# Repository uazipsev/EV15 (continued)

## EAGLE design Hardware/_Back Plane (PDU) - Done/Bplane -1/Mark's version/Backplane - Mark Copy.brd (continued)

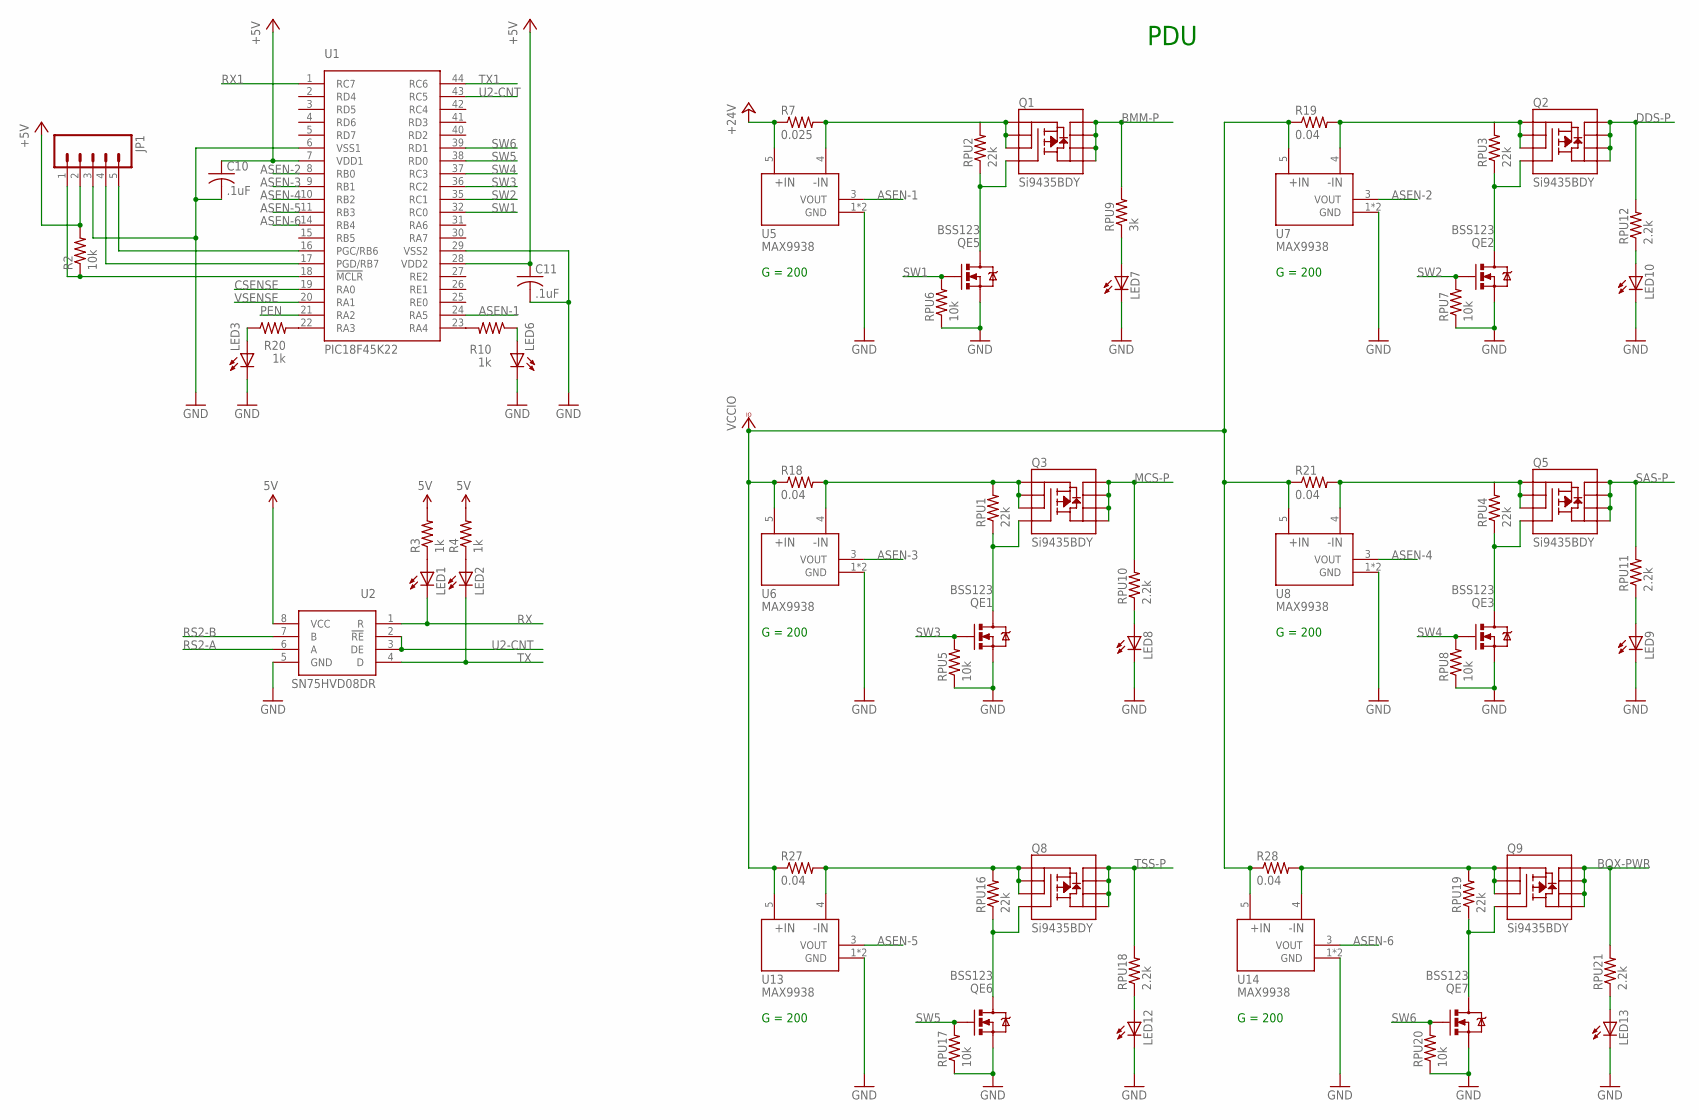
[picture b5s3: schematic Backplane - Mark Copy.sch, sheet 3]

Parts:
C10, C11: .1uF; C0805
JP1: M05LOCK_LONGPADS; 1X05_LOCK_LONGPADS
LED1, LED2, LED3, LED6, LED7, LED8, LED9, LED10, LED12, LED13: LEDCHIP-LED0805; CHIP-LED0805
Q1, Q2, Q3, Q5, Q8, Q9: Si9435BDY; SO08
QE1, QE2, QE3, QE5, QE6, QE7: BSS123; SOT-23
R2: 10k; 0805
R3, R4, R10, R20: 1k; R0805
R7: 0.025; R6332
R18, R19, R21, R27, R28: 0.04; R6332
RPU1, RPU2, RPU3, RPU4, RPU16, RPU19: 22k; 0805
RPU5, RPU6, RPU7, RPU8, RPU17, RPU20: 10k; 0805
RPU9: 3k; 0805
RPU10, RPU11, RPU12, RPU18, RPU21: 2.2k; 0805
U1: PIC18F45K22; TQFP-44
U2: SN75HVD08DR; SO-8
U5, U6, U7, U8, U13, U14: MAX9938; SOT23-5

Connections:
5V: R3.2, R4.2, U2.8 (VCC); also elsewhere on the board
+5V: C10.1, C11.1, JP1.2, R2.2, U1.7 (VDD1), U1.28 (VDD2); also elsewhere on the board
+24V: R7.1, U5.5 (+IN); also elsewhere on the board
ASEN-1: U1.24 (RA5), U5.3 (VOUT)
ASEN-2: U1.8 (RB0), U7.3 (VOUT)
ASEN-3: U1.9 (RB1), U6.3 (VOUT)
ASEN-4: U1.10 (RB2), U8.3 (VOUT)
ASEN-5: U1.11 (RB3), U13.3 (VOUT)
ASEN-6: U1.14 (RB4), U14.3 (VOUT)
BMM-P: Q1.5 (D), Q1.6 (D), Q1.7 (D), Q1.8 (D), RPU9.2; also elsewhere on the board
BOX-PWR: Q9.5 (D), Q9.6 (D), Q9.7 (D), Q9.8 (D), RPU21.2; also elsewhere on the board
CSENSE: U1.19 (RA0); also elsewhere on the board
DDS-P: Q2.5 (D), Q2.6 (D), Q2.7 (D), Q2.8 (D), RPU12.2; also elsewhere on the board
GND: C10.2, C11.2, JP1.3, LED3.C, LED6.C, LED7.C, LED8.C, LED9.C, LED10.C, LED12.C, LED13.C, QE1.2 (S), QE2.2 (S), QE3.2 (S), QE5.2 (S), QE6.2 (S), QE7.2 (S), RPU5.1, RPU6.1, RPU7.1, RPU8.1, RPU17.1, RPU20.1, U1.6 (VSS1), U1.29 (VSS2), U2.5 (GND), U5.1 (GND), U5.2 (GND), U6.1 (GND), U6.2 (GND), U7.1 (GND), U7.2 (GND), U8.1 (GND), U8.2 (GND), U13.1 (GND), U13.2 (GND), U14.1 (GND), U14.2 (GND); also elsewhere on the board
MCS-P: Q3.5 (D), Q3.6 (D), Q3.7 (D), Q3.8 (D), RPU10.2; also elsewhere on the board
unnamed: Q1.4 (G), QE5.3 (D), RPU2.1
unnamed: Q8.1 (S), Q8.2 (S), Q8.3 (S), R27.2, RPU16.2, U13.4 (-IN)
unnamed: Q3.1 (S), Q3.2 (S), Q3.3 (S), R18.2, RPU1.2, U6.4 (-IN)
unnamed: Q3.4 (G), QE1.3 (D), RPU1.1
unnamed: Q2.1 (S), Q2.2 (S), Q2.3 (S), R19.2, RPU3.2, U7.4 (-IN)
unnamed: LED3.A, R20.1
unnamed: LED7.A, RPU9.1
unnamed: Q2.4 (G), QE2.3 (D), RPU3.1
unnamed: R20.2, U1.22 (RA3)
unnamed: LED8.A, RPU10.1
unnamed: LED9.A, RPU11.1
unnamed: LED1.A, R3.1
unnamed: LED2.A, R4.1
unnamed: Q5.1 (S), Q5.2 (S), Q5.3 (S), R21.2, RPU4.2, U8.4 (-IN)
unnamed: Q5.4 (G), QE3.3 (D), RPU4.1
unnamed: LED10.A, RPU12.1
unnamed: Q8.4 (G), QE6.3 (D), RPU16.1
unnamed: Q1.1 (S), Q1.2 (S), Q1.3 (S), R7.2, RPU2.2, U5.4 (-IN)
unnamed: LED12.A, RPU18.1
unnamed: Q9.1 (S), Q9.2 (S), Q9.3 (S), R28.2, RPU19.2, U14.4 (-IN)
unnamed: Q9.4 (G), QE7.3 (D), RPU19.1
unnamed: JP1.4, U1.17 (PGD/RB7)
unnamed: JP1.5, U1.16 (PGC/RB6)
unnamed: LED13.A, RPU21.1
unnamed: JP1.1, R2.1, U1.18 (!MCLR)
unnamed: LED6.A, R10.1
unnamed: R10.2, U1.23 (RA4)
PEN: U1.21 (RA2)
RS2-A: U2.6 (A); also elsewhere on the board
RS2-B: U2.7 (B); also elsewhere on the board
RX: LED1.C, U2.1 (R)
RX1: U1.1 (RC7)
SAS-P: Q5.5 (D), Q5.6 (D), Q5.7 (D), Q5.8 (D), RPU11.2; also elsewhere on the board
SW1: QE5.1 (G), RPU6.2, U1.32 (RC0)
SW2: QE2.1 (G), RPU7.2, U1.35 (RC1)
SW3: QE1.1 (G), RPU5.2, U1.36 (RC2)
SW4: QE3.1 (G), RPU8.2, U1.37 (RC3)
SW5: QE6.1 (G), RPU17.2, U1.38 (RD0)
SW6: QE7.1 (G), RPU20.2, U1.39 (RD1)
TSS-P: Q8.5 (D), Q8.6 (D), Q8.7 (D), Q8.8 (D), RPU18.2; also elsewhere on the board
TX: LED2.C, U2.4 (D)
TX1: U1.44 (RC6)
U2-CNT: U1.43 (RC5), U2.2 (!RE), U2.3 (DE)
VCCIO: R18.1, R19.1, R21.1, R27.1, R28.1, U6.5 (+IN), U7.5 (+IN), U8.5 (+IN), U13.5 (+IN), U14.5 (+IN); also elsewhere on the board
VSENSE: U1.20 (RA1); also elsewhere on the board

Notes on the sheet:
PDU
G = 200

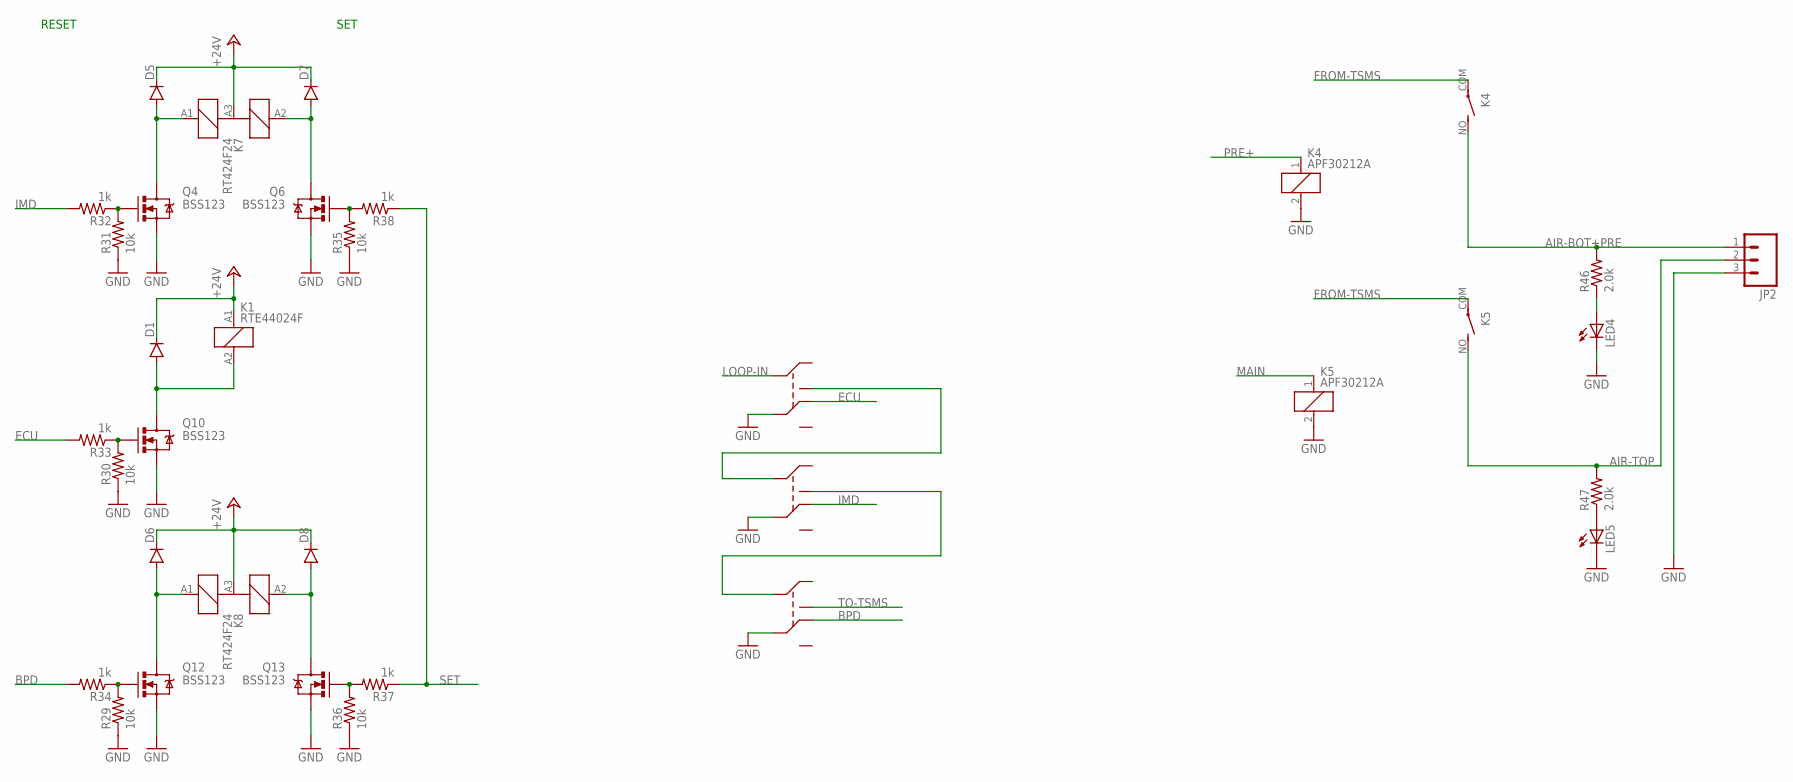
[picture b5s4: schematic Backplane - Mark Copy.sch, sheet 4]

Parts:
D1, D5, D6, D7, D8: DIODESMA-KIT; SMA-DIODE-KIT
JP2: M03POLAR_LOCK; MOLEX-1X3_LOCK
K1: RTE44024F
K4, K5: APF30212A
K7, K8: RT424F24
LED4, LED5: LEDCHIPLED_0805; CHIPLED_0805
Q4, Q6, Q10, Q12, Q13: BSS123; SOT23-3
R29, R30, R31, R35, R36: 10k; 0805
R32, R33, R34, R37, R38: 1k; 0805
R46, R47: 2.0k; 0805

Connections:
+24V: D1.C, D5.C, D6.C, D7.C, D8.C, K1.A1 (+), K7.A3 (-), K8.A3 (-); also elsewhere on the board
AIR-BOT+PRE: JP2.1, K4.NO (S), R46.2
AIR-TOP: JP2.2, K5.NO (S), R47.2
BPD: R34.2; also elsewhere on the board
ECU: K1.22 (NC2), R33.2; also elsewhere on the board
FROM-TSMS: K4.COM, K5.COM; also elsewhere on the board
GND: JP2.3, K1.21 (C2), K4.2, K5.2, K7.21 (C2), K8.21 (C2), LED4.C, LED5.C, Q4.2 (S), Q6.2 (S), Q10.2 (S), Q12.2 (S), Q13.2 (S), R29.1, R30.1, R31.1, R35.1, R36.1; also elsewhere on the board
IMD: K7.22 (NC2), R32.2; also elsewhere on the board
LOOP-IN: K1.11 (C1); also elsewhere on the board
MAIN: K5.1; also elsewhere on the board
unnamed: Q4.1 (G), R31.2, R32.1
unnamed: K1.14 (NO1), K7.11 (C1)
unnamed: K7.14 (NO1), K8.11 (C1)
unnamed: Q6.1 (G), R35.2, R38.2
unnamed: D1.A, K1.A2 (-), Q10.3 (D)
unnamed: D5.A, K7.A1 (+1), Q4.3 (D)
unnamed: Q10.1 (G), R30.2, R33.1
unnamed: D7.A, K7.A2 (+2), Q6.3 (D)
unnamed: D6.A, K8.A1 (+1), Q12.3 (D)
unnamed: D8.A, K8.A2 (+2), Q13.3 (D)
unnamed: Q13.1 (G), R36.2, R37.2
unnamed: Q12.1 (G), R29.2, R34.1
unnamed: LED4.A, R46.1
unnamed: LED5.A, R47.1
PRE+: K4.1; also elsewhere on the board
SET: R37.1, R38.1
TO-TSMS: K8.14 (NO1); also elsewhere on the board

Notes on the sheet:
RESET
SET

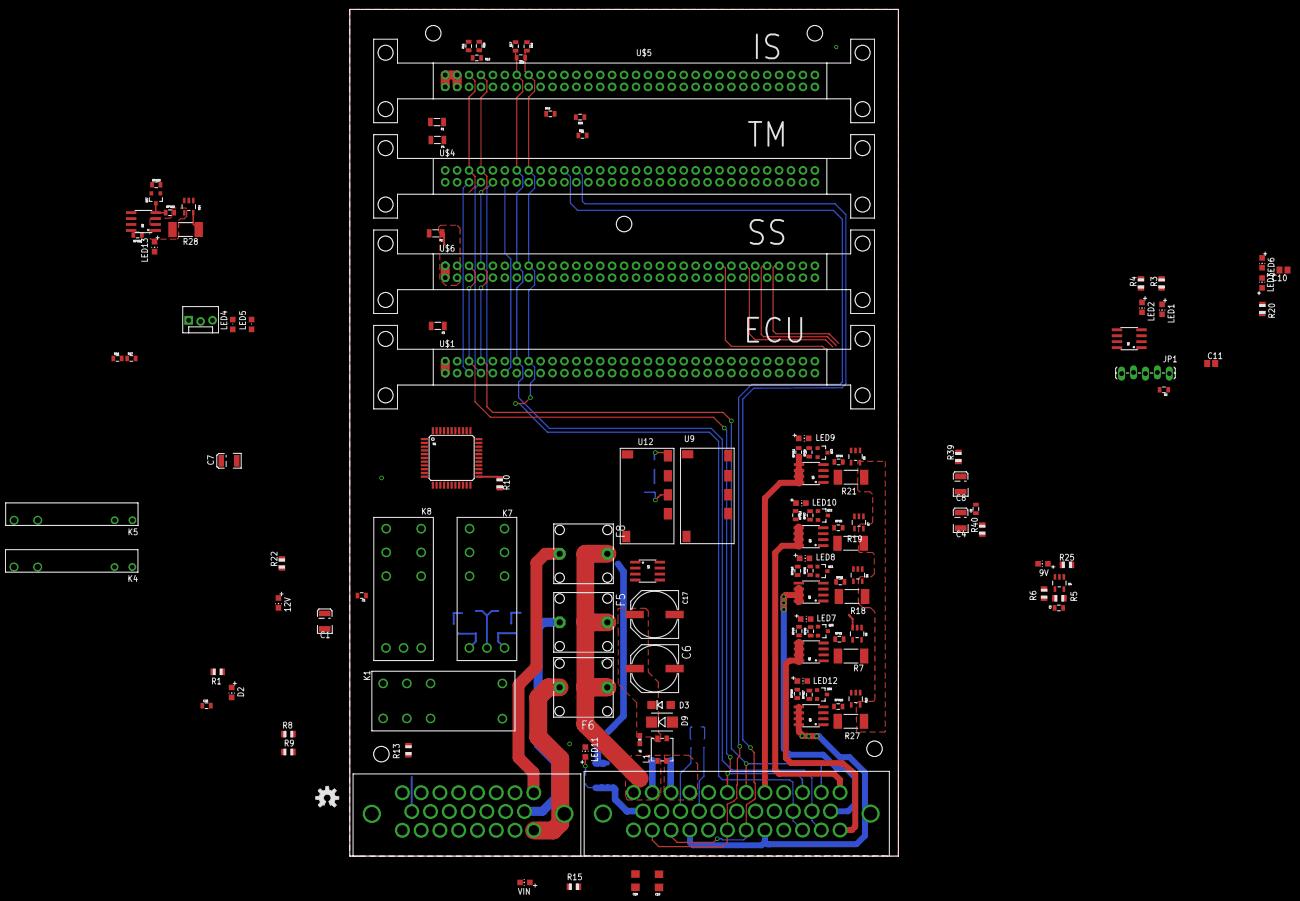
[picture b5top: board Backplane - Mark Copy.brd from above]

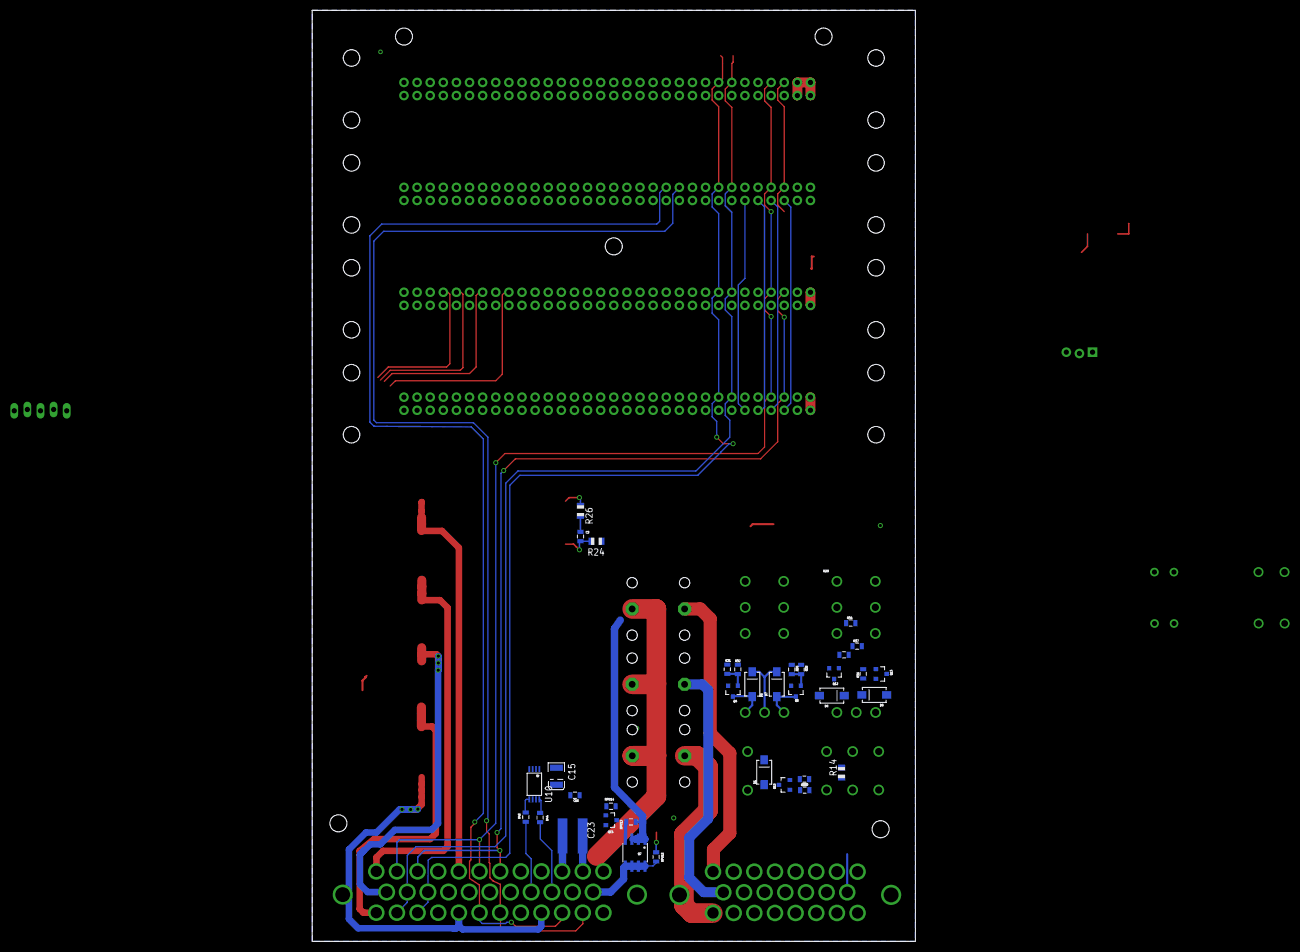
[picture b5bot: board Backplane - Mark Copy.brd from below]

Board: 2 copper layers, 116.8 x 180.3 mm, 171 parts (35 on the bottom side), 129 nets.

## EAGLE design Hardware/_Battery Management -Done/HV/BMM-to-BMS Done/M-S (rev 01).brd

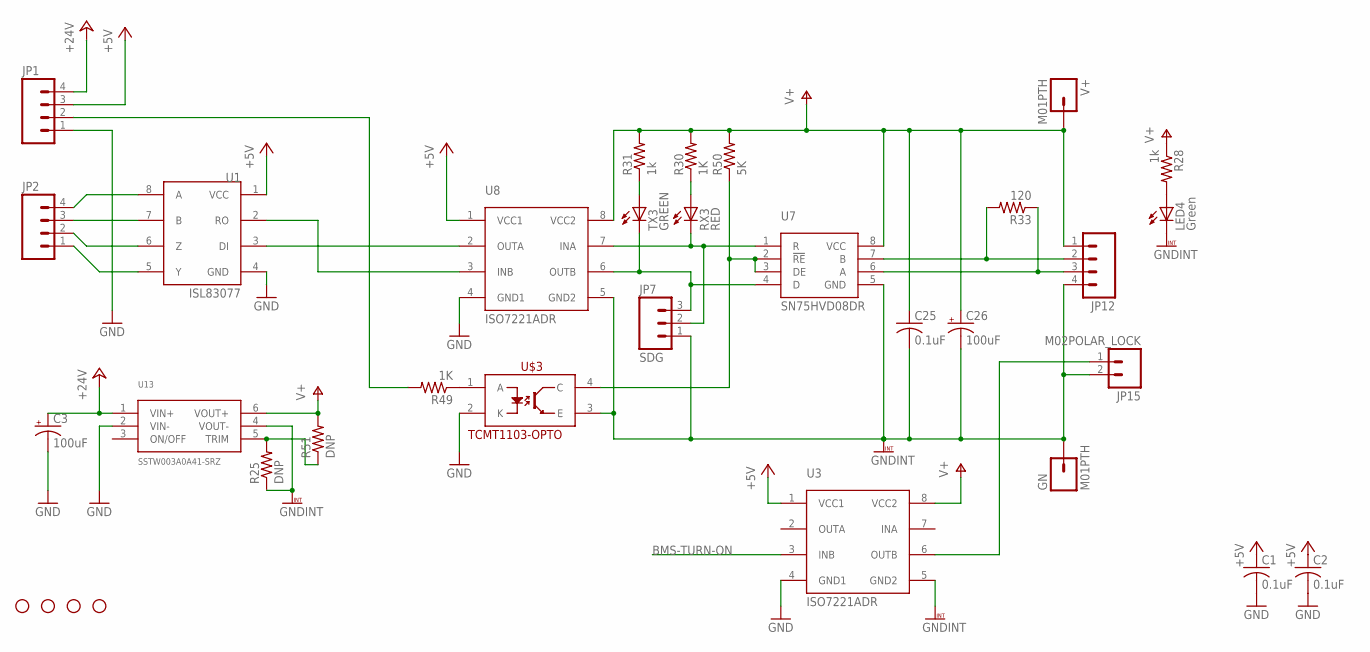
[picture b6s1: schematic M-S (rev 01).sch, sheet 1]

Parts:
C1, C2, C25: 0.1uF; C0805
C3, C26: 100uF; C/6032-28W
GN: M01PTH; 1X01
JP1, JP2, JP12: M04POLAR_LOCK; MOLEX-1X4_LOCK
JP7: SDG; 1X03_LOCK_LONGPADS
JP15: M02POLAR_LOCK; MOLEX-1X2_LOCK
LED4: Green; CHIPLED_0805
R25, R51: DNP; R0805
R28, R31: 1k; R0805
R30, R49: 1K; R0805
R33: 120; R0805
R50: 5K; R0805
RX3: RED; CHIPLED_0805
STANDOFF1, STANDOFF2, STANDOFF3, STANDOFF4: STAND-OFF
TX3: GREEN; CHIPLED_0805
U1: ISL83077; SO08
U3, U8: ISO7221ADR; SOIC-8
U7: SN75HVD08DR; SO-8
U13: SSTW003A0A41-SRZ
U$3: TCMT1103-OPTO; SSOP-4
V+: M01PTH; 1X01

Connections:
+5V: C1.1, C2.1, JP1.3, U1.1 (VCC), U3.1 (VCC1), U8.1 (VCC1); also elsewhere on the board
+24V: C3.+, JP1.4, U13.1 (VIN+)
BMS-TURN-ON: U3.3 (INB); also elsewhere on the board
GND: C1.2, C2.2, C3.-, JP1.1, U1.4 (GND), U3.4 (GND1), U8.4 (GND1), U13.2 (VIN-), U$3.2 (K); also elsewhere on the board
GNDINT: C25.2, C26.-, GN.1, JP7.1, JP12.4, JP15.2, LED4.C, R25.1, U3.5 (GND2), U7.5 (GND), U8.5 (GND2), U13.4 (VOUT-), U$3.3 (E)
unnamed: U1.3 (DI), U8.2 (OUTA)
unnamed: U1.2 (RO), U8.3 (INB)
unnamed: JP2.4, U1.8 (A)
unnamed: JP2.3, U1.7 (B)
unnamed: JP2.2, U1.6 (Z)
unnamed: JP2.1, U1.5 (Y)
unnamed: JP1.2, R49.2
unnamed: JP15.1, U3.6 (OUTB)
unnamed: JP12.2, R33.2, U7.7 (B)
unnamed: JP12.3, R33.1, U7.6 (A)
unnamed: R25.2, R51.1, U13.5 (TRIM)
unnamed: LED4.A, R28.2
unnamed: R49.1, U$3.1 (A)
unnamed: R50.1, U7.2 (!RE), U7.3 (DE), U$3.4 (C)
unnamed: R30.1, RX3.A
unnamed: R31.1, TX3.A
PIC1: JP7.2, RX3.C, U7.1 (R), U8.7 (INA)
PIC2: JP7.3, TX3.C, U7.4 (D), U8.6 (OUTB)
V+: C25.1, C26.+, JP12.1, R28.1, R30.2, R31.2, R50.2, R51.2, U3.8 (VCC2), U7.8 (VCC), U8.8 (VCC2), U13.6 (VOUT+), V+.1

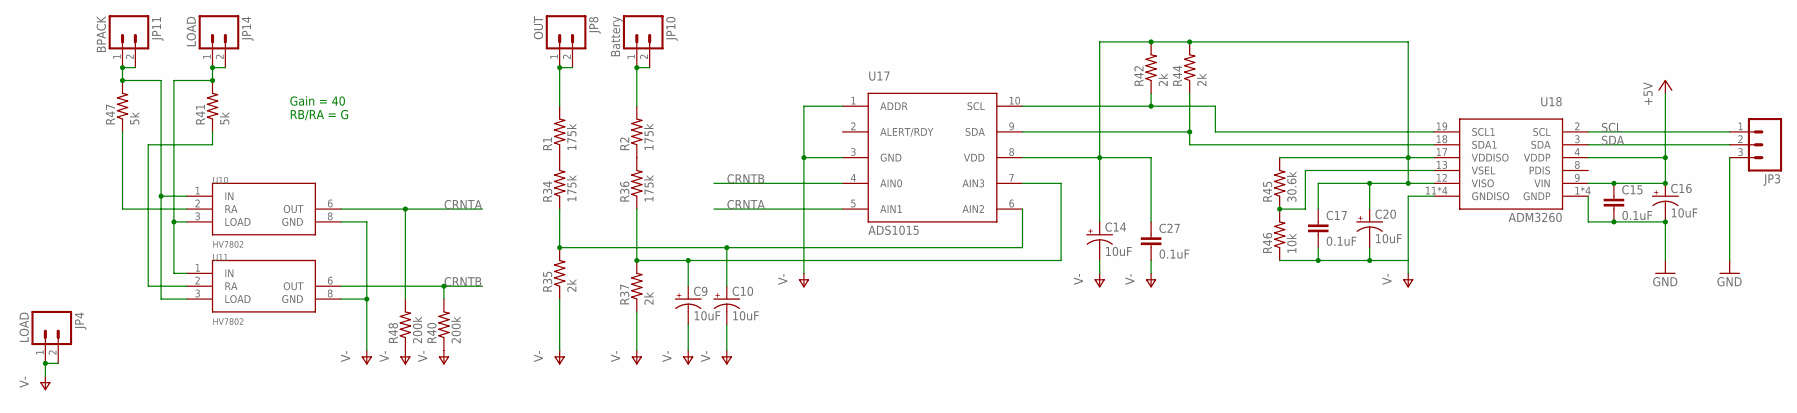
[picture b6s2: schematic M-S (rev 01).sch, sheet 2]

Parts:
C9, C10, C14, C16, C20: 10uF; EIA3216
C15, C17, C27: 0.1uF; 0805
JP3: M03POLAR_LOCK; MOLEX-1X3_LOCK
JP4, JP14: LOAD; MOLEX-1X2_LOCK
JP8: OUT; MOLEX-1X2_LOCK
JP10: Battery; MOLEX-1X2_LOCK
JP11: BPACK; MOLEX-1X2_LOCK
R1, R2, R34, R36: 175k; 1206
R35, R37: 2k; 1206
R40, R48: 200k; 0805
R41, R47: 5k; 0805
R42, R44: 2k; 0805
R45: 30.6k; 0805
R46: 10k; 0805
U10, U11: HV7802; MSOP-8
U17: ADS1015; MSOP-10
U18: ADM3260; SSOP-20

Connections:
+5V: C15.1, C16.A (+), U18.4 (VDDP), U18.9 (VIN); also elsewhere on the board
CRNTA: R48.2, U10.6 (OUT), U17.5 (AIN1)
CRNTB: R40.2, U11.6 (OUT), U17.4 (AIN0)
GND: C15.2, C16.C (-), JP3.3, U18.1 (GNDP), U18.5 (GNDP), U18.7 (GNDP), U18.10 (GNDP); also elsewhere on the board
unnamed: R41.1, U11.2 (RA)
unnamed: R47.1, U10.2 (RA)
unnamed: R1.1, R34.2
unnamed: JP14.1, JP14.2, R41.2, U10.3 (LOAD), U11.1 (IN)
unnamed: R2.1, R36.2
unnamed: JP8.1, JP8.2, R1.2
unnamed: JP11.1, JP11.2, R47.2, U10.1 (IN), U11.3 (LOAD)
unnamed: C10.A (+), R34.1, R35.2, U17.6 (AIN2)
unnamed: JP10.1, JP10.2, R2.2
unnamed: C9.A (+), R36.1, R37.2, U17.7 (AIN3)
unnamed: C14.A (+), C17.1, C20.A (+), C27.1, R42.2, R44.2, R45.2, U17.8 (VDD), U18.12 (VISO), U18.17 (VDDISO)
unnamed: R42.1, U17.10 (SCL), U18.19 (SCL1)
unnamed: R44.1, U17.9 (SDA), U18.18 (SDA1)
unnamed: R45.1, R46.2, U18.13 (VSEL)
SCL: JP3.1, U18.2 (SCL)
SDA: JP3.2, U18.3 (SDA)
V-: C9.C (-), C10.C (-), C14.C (-), C17.2, C20.C (-), C27.2, JP4.1, JP4.2, R35.1, R37.1, R40.1, R46.1, R48.1, U10.8 (GND), U11.8 (GND), U17.1 (ADDR), U17.3 (GND), U18.11 (GNDISO), U18.14 (GNDISO), U18.16 (GNDISO), U18.20 (GNDISO); also elsewhere on the board

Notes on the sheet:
Gain = 40 RB/RA = G

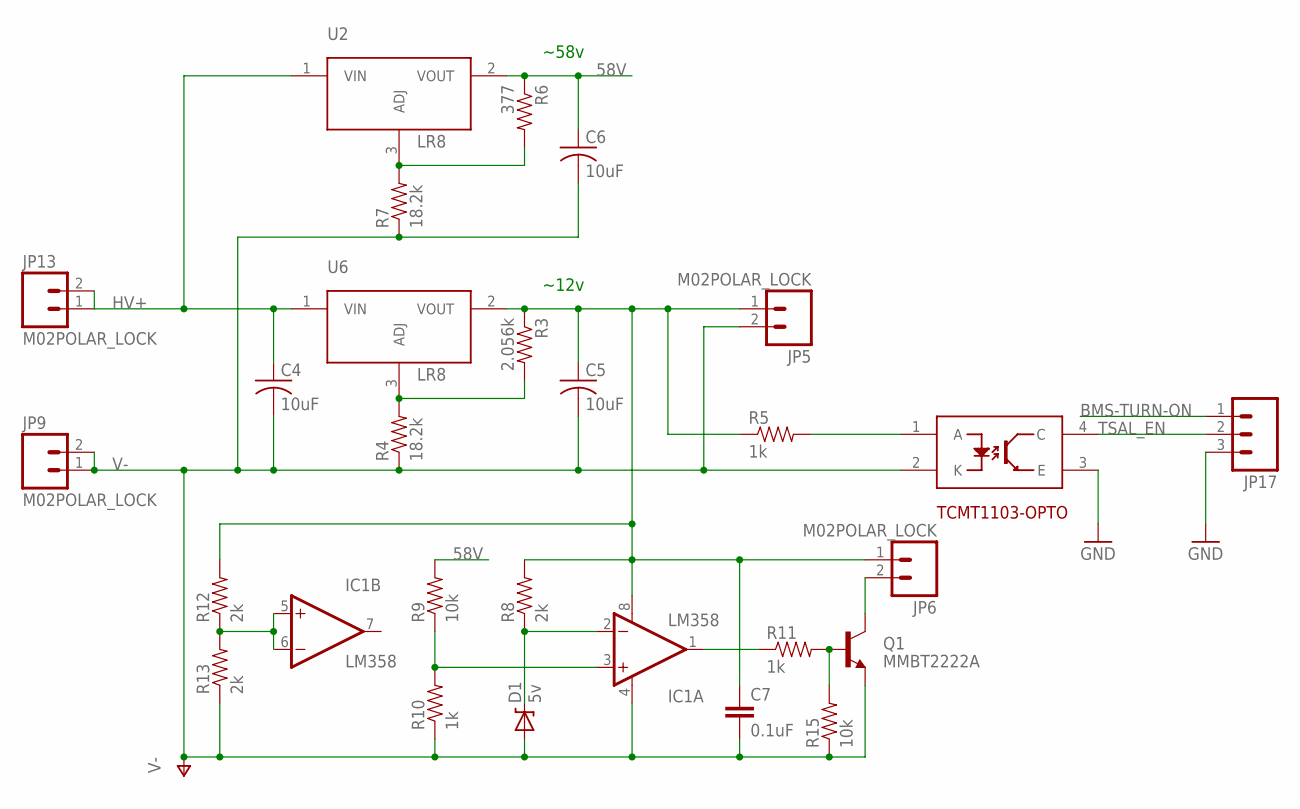
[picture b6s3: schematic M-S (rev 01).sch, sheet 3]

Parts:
C4: 10uF; C050-030X075
C5, C6: 10uF; C0805
C7: 0.1uF; 0805
D1: 5v; SOD-323@1
IC1: LM358; SO08
JP5, JP6, JP9, JP13: M02POLAR_LOCK; MOLEX-1X2_LOCK
JP17: M03POLAR_LOCK; MOLEX-1X3_LOCK
Q1: MMBT2222A; SOT23
R3: 2.056k; 0805
R4, R7: 18.2k; 0805
R5, R10, R11: 1k; 0805
R6: 377; 0805
R8, R12, R13: 2k; 0805
R9, R15: 10k; 0805
U2, U6: LR8; DPAK
U$11: TCMT1103-OPTO; SSOP-4

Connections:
58V: C6.1, R6.1, R9.2, U2.2 (VOUT)
BMS-TURN-ON: JP17.1; also elsewhere on the board
GND: JP17.3, U$11.3 (E); also elsewhere on the board
HV+: C4.1, JP13.1, JP13.2, U2.1 (VIN), U6.1 (VIN)
unnamed: R6.2, R7.2, U2.3 (ADJ)
unnamed: D1.1 (C), IC1.2 (-IN), R8.1
unnamed: IC1.3 (+IN), R9.1, R10.2
unnamed: R5.2, U$11.1 (A)
unnamed: IC1.1 (OUT), R11.1
unnamed: Q1.1 (B), R11.2, R15.2
unnamed: JP6.2, Q1.3 (C)
unnamed: IC1.5 (+IN), IC1.6 (-IN), R12.1, R13.2
unnamed: C5.1, C7.1, IC1.8 (V+), JP5.1, JP6.1, R3.1, R5.1, R8.2, R12.2, U6.2 (VOUT)
unnamed: R3.2, R4.2, U6.3 (ADJ)
TSAL_EN: JP17.2, U$11.4 (C)
V-: C4.2, C5.2, C6.2, C7.2, D1.2 (A), IC1.4 (V-), JP5.2, JP9.1, JP9.2, Q1.2 (E), R4.1, R7.1, R10.1, R13.1, R15.1, U$11.2 (K); also elsewhere on the board

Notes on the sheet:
~12v
~58v

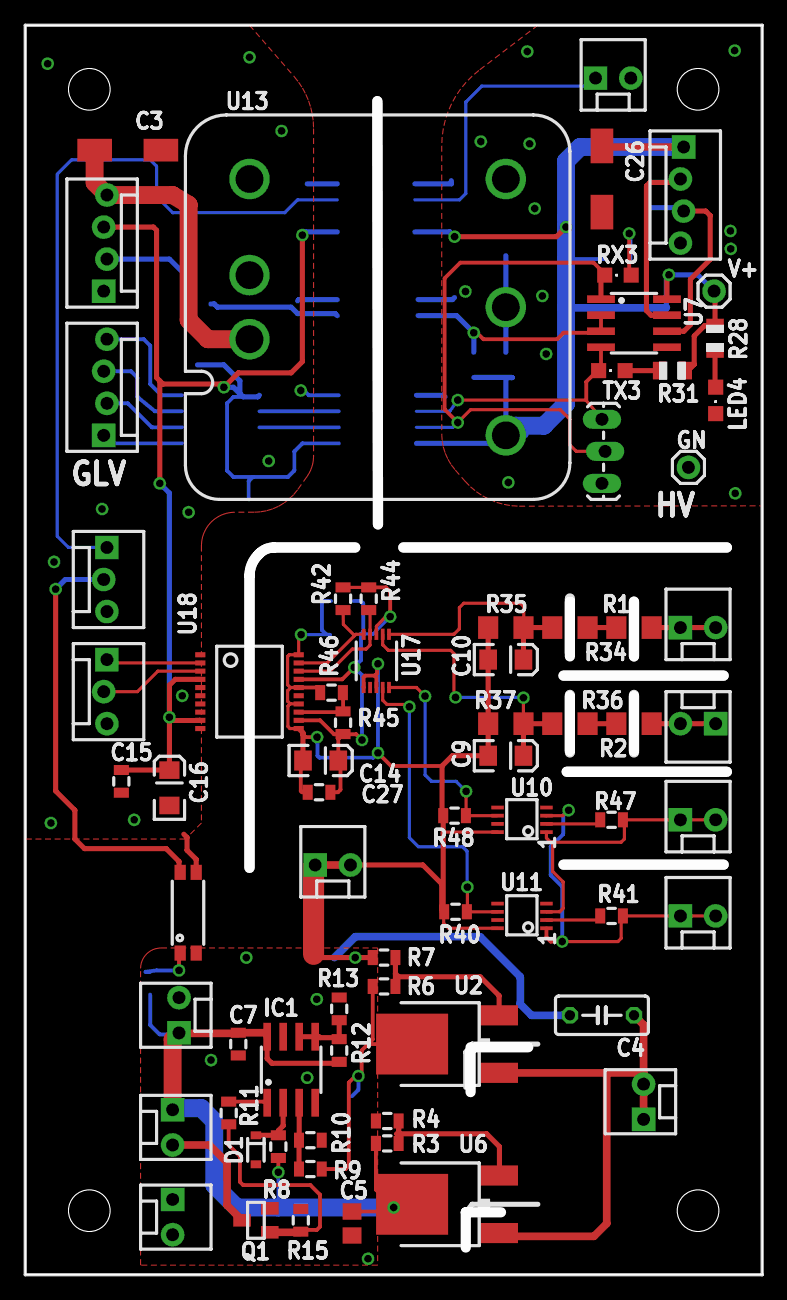
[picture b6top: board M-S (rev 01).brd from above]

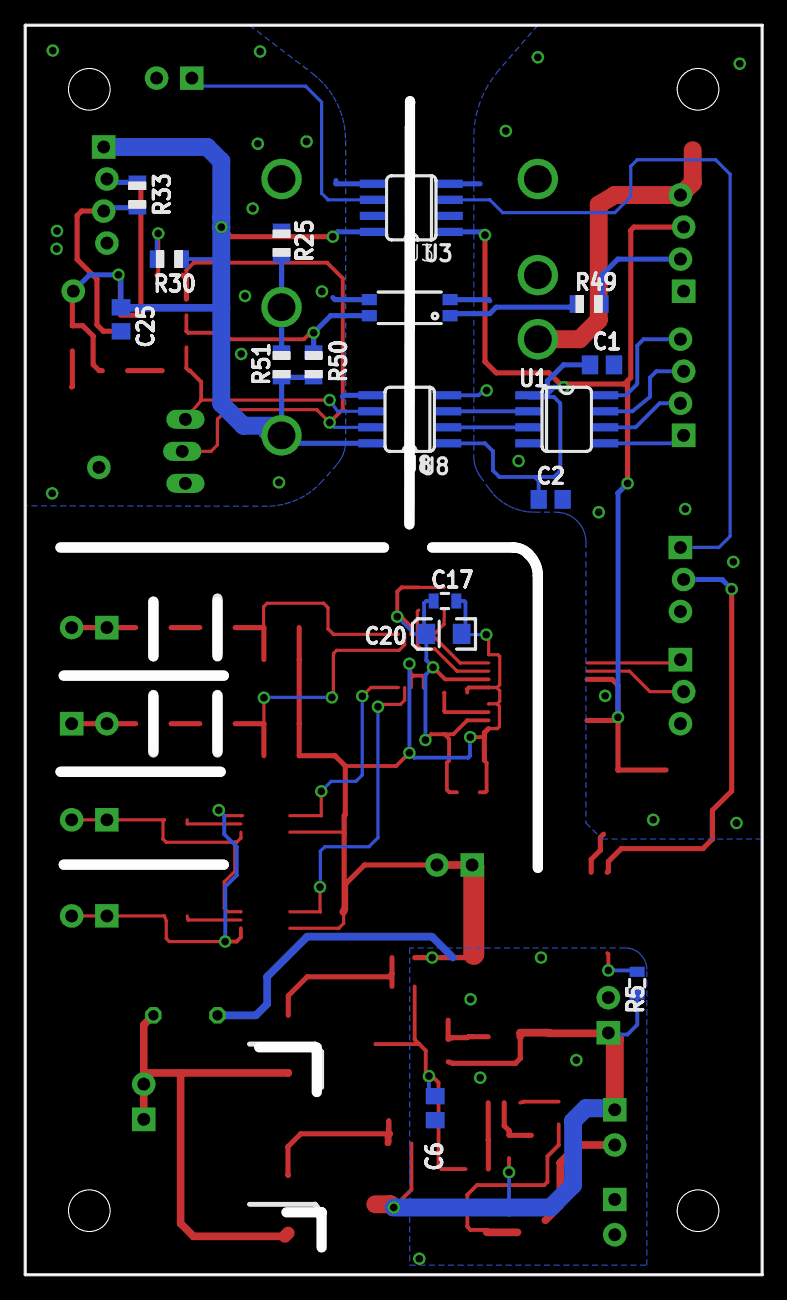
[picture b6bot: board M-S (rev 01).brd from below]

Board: 2 copper layers, 58.4 x 99.1 mm, 92 parts (17 on the bottom side), 56 nets.

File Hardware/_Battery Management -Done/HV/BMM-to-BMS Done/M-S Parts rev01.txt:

type	qty	Part	Value	Device	Package	Library	notes
resistor	1	R33	120	R-US_R0805	R0805	adafruit	
resistor	1	R6	377	RESISTOR0805-RES	805	SparkFun-Passives	
cap		C1	0.1uF	C-USC0805	C0805	rcl	how many different caps are here
		C2	0.1uF	C-USC0805	C0805	rcl	
		C7	0.1uF	0.1UF-25V-5%(0603	)      0603-CAP	SparkFun-Capacitors	
		C15	0.1uF	CAP0805	805	SparkFun-Capacitors	
		C17	0.1uF	CAP0805	805	SparkFun-Capacitors	
		C25	0.1uF	C-USC0805	C0805	rcl	
		C27	0.1uF	CAP0805	805	SparkFun-Capacitors	
cap	2	"C3, C26"	100uF	CPOL-USC/6032-28W	C/6032-28W	rcl	
resistor	3	"R9, R15, R46"	10k	RESISTOR0805-RES	805	SparkFun-Passives	
		C4	10uF	C-US050-030X075	C050-030X075	rcl	
		C5	10uF	C-USC0805	C0805	rcl	
		C6	10uF	C-USC0805	C0805	rcl	
cap	5	"C9, C10, C14, C16, C20"	10uF	CAP_POL1206	EIA3216	SparkFun-Capacitors	
resistor	4	"R1, R2, R34, R36"	175k	RESISTOR1206	1206	SparkFun-Passives	
resistor	2	"R4, R7"	18.2k	RESISTOR0805-RES	805	SparkFun-Passives	
resistor	6	"R5, R10, R28, R30, R31, R49"	1k	RESISTOR0805-RES	805	SparkFun-Passives	
resistor	2	"R3, R11"	2.056k	RESISTOR0805-RES	805	SparkFun-Passives	
resistor	2	"R40, R48"	200k	RESISTOR0805-RES	805	SparkFun-Passives	
resistor	7	"R8, R12, R13, R35, R37, R42, R44"	2k	RESISTOR0805-RES	805	SparkFun-Passives	
resistor	1	R45	30.6k	RESISTOR0805-RES	805	SparkFun-Passives	
resistor	3	"R41, R47, R50"	5k	RESISTOR0805-RES	805	SparkFun-Passives	
diode	1	U$1	5v	DIODE-ZENER-BZT52	SOD-323@1	SparkFun-DiscreteSemi	
ic	1	U18	ADM3260	ADM3260	SSOP-20	FSAE Eletric	
ic	1	U17	ADS1015	ADS1015	MSOP-10	NASA_LIB	
conn	2	"JP10, JP11"	Battery	M02POLAR_LOCK	MOLEX-1X2_LOCK	SparkFun-Connectors	
		R25	DNP	R-US_R0805	R0805	adafruit	what size is this so we can buy the part
		R51	DNP	R-US_R0805	R0805	adafruit	what size is this so we can buy the part
LED		"LED4, TX3"	Green	LEDCHIPLED_0805	CHIPLED_0805	adafruit	
ic	2	"U10, U11"	HV7802	HV7802	MSOP-8	FSAE Eletric	
		U1	ISL83077	ISL83077	SO08	NASA_LIB	
		U8	ISO7221A	DR       ISO7221ADR	SOIC-8	Gasbarre	
		IC1	LM358	OPAMP-DUALU	SO08	SparkFun-AnalogIC	
		JP4	LOAD	M02POLAR_LOCK	MOLEX-1X2_LOCK	SparkFun-Connectors	
		JP14	LOAD	M02POLAR_LOCK	MOLEX-1X2_LOCK	SparkFun-Connectors	
		U2	LR8	LR8	DPAK	FSAE Eletric	
		U6	LR8	LR8	DPAK	FSAE Eletric	
		GN	M01PTH	M01PTH	1X01	SparkFun-Connectors	
		V+	M01PTH	M01PTH	1X01	SparkFun-Connectors	
		JP5	M02POLAR	_LOCK    M02POLAR_LOCK	MOLEX-1X2_LOCK	SparkFun-Connectors	
		JP6	M02POLAR	_LOCK    M02POLAR_LOCK	MOLEX-1X2_LOCK	SparkFun-Connectors	
		JP9	M02POLAR	_LOCK    M02POLAR_LOCK	MOLEX-1X2_LOCK	SparkFun-Connectors	
		JP13	M02POLAR	_LOCK    M02POLAR_LOCK	MOLEX-1X2_LOCK	SparkFun-Connectors	
		Q1	MMBT2222	A        TRANSISTOR_NPNMMB	T2222A SOT23	SparkFun-DiscreteSemi	
		JP8	OUT	M02POLAR_LOCK	MOLEX-1X2_LOCK	SparkFun-Connectors	
		RX3	RED	LEDCHIPLED_0805	CHIPLED_0805	adafruit	
		JP7	SDG	M03LOCK_LONGPADS	1X03_LOCK_LONGPADS	SparkFun-Connectors	
		U7	SN75HVD0	8DR      SN75HVD08DR	SO-8	FSAE Eletric	
		U13	SSTW003A	0A41-SRZ SSTW003A0A41-SRZ	SSTW003A0A41-SRZ	FSAE Eletric	
		U$3	TCMT1103	#NAME?	SSOP-4	SparkFun-DiscreteSemi	
		U$11	TCMT1103	#NAME?	SSOP-4	SparkFun-DiscreteSemi	
		JP1		M04POLAR_LOCK	MOLEX-1X4_LOCK	SparkFun-Connectors	
		JP2		M04POLAR_LOCK	MOLEX-1X4_LOCK	SparkFun-Connectors	
		JP3		M03POLAR_LOCK	MOLEX-1X3_LOCK	SparkFun-Connectors	
		JP12		M04POLAR_LOCK	MOLEX-1X4_LOCK	SparkFun-Connectors	
		JP15		M02POLAR_LOCK	MOLEX-1X2_LOCK	SparkFun-Connectors
